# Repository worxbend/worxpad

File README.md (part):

# worxpad

A wireless macropad on its own PCB in a CNC aluminium case. 16 low-profile keys, two knobs with push, two round
buttons, a 240 x 240 colour display, USB-C and Bluetooth to four hosts, a 1,200 mAh battery. Board, case and
firmware are generated from code in this repository and checked against one shared file,
[`board.toml`](board.toml).

It has the function set of the Prota Designs GLYF, which serves as a reference only. Nothing of the GLYF's
name, artwork, firmware or files is used. Where worxpad differs, and why, is in
[Compared with the GLYF](#compared-with-the-glyf) and [docs/reference-device.md](docs/reference-device.md).

*A render of the case model, not a photo. The screen shows a drawing of what the firmware should display.*

> **Status: design files only. Nothing has been built, and the design is not finished.**
> The PCB is placed and routed (DRC clean), but its order files have not been written yet. Two case checks fail. No board has been ordered, no case printed or milled, and the firmware has never
> run on a chip. Every number below is what the design files and their automatic checks say. Read
> [Before you order](#before-you-order) first.

## Contents

1. [Status](#status)
2. [What it is](#what-it-is)
3. [Gallery](#gallery)
4. [Build one](#build-one)
5. [Stock keymap](#stock-keymap)
6. [Work on the design](#work-on-the-design)
7. [What is checked](#what-is-checked)
8. [Where things are](#where-things-are)
9. [Before you order](#before-you-order)
10. [Compared with the GLYF](#compared-with-the-glyf)
11. [License](#license)

## Status

Checked on 2026-11-13. The commands marked "run" were run on this repository for this table. The others are
copied from the last builder run and its report, named in the last column.

| Part | State | How it was checked |
| --- | --- | --- |
| Research and decisions | Done. Seven decision records, a parts summary, a reference dossier; 40 design decisions. | Read; [docs/decisions.md](docs/decisions.md) |
| Specification | Done. `board.toml`: outline, keys, controls, display, module, ports, battery, screws, stack-up, pin map, panel. | Run: `python3 tools/check_spec.py`, 92 of 92 pass |
| Circuit and schematic | Done. 107 parts, 74 nets, 61 machine-placed (31 LCSC codes). Generated KiCad 10 sheet. ERC: 0 errors, 0 warnings. 309 pins match the circuit. | Run: `make pcb-test`, 73 unit tests pass. ERC from the last `build.py schematic`, [pcb/README.md](pcb/README.md) |
| Pin map | Circuit and firmware agree with `board.toml`. | Run: `python3 tools/check_pins.py`, 0 circuit failures, 12 of 12 firmware checks |
| PCB layout | Routed. All 107 parts placed on 4 layers. 1,980 tracks, 280 vias, 0 pads unrouted; short signal hops on both inner layers. DRC: 0 errors, 0 unconnected, 0 schematic differences. No copper in the antenna keep-out. | Run: `make pcb-place` and `make pcb-check`, exit 0 (2026-11-14); `pcb/routing.txt`, [pcb/README.md](pcb/README.md#routing) |
| Board order files | Written. JLCPCB and PCBWay packages, 61 placements in 30 BOM lines (56 on the bottom), panel 135.65 x 95.30 mm with 0 DRC errors, board STEP 1.616 mm thick. | Run: `make pcb-fab`, exit 0 (2026-11-14); [pcb/README.md](pcb/README.md#checks) |
| Case | Model done. 177 of 177 limit checks pass. G1 and G2 pass (tip 0.45 mm against 0.4) only with a proposed bottoming tap that D6 does not yet record. 24 of 24 parts valid, 0 clashes in 666 (CNC) and 703 (FDM) part pairs. Self-test 26 of 26. | Run: `make cad-check` (exit 0); `cad/exports/checks.json`, [cad/README.md](cad/README.md#checks) |
| Firmware | Builds. ZMK 4dd95d78 on Zephyr 10ba6d0c (pinned in `west.yml`). FLASH 391,548 B of 811,008 B (48.28 %), RAM 122,322 B of 262,144 B (46.66 %). UF2 is 783,360 B. | Run: `bash firmware/build.sh` (exit 0); [firmware/README.md](firmware/README.md#build) |
| Pictures | Done. 7 stills, the status screen and a 72-frame turntable; PCB and case pictures. The PCB pictures in `docs/images/pcb/` show the routed board. The renders in `docs/images/renders/` use the routed board's STEP for the board; its parts are still the case package's reference shapes, because the STEP holds no part solids FreeCAD can read. | Run: `make renders`, exit 0 in 1,014 s (2026-11-14) |
| Order package | Files complete. 34 files listed, 0 problems; 30 BOM lines, 61 placements. The gates in [Before you order](#before-you-order) are still open. | Run: `python3 tools/order_package.py`, exit 0 (2026-11-14); [production/README.md](production/README.md) |
| Documentation | Every path and anchor named in Markdown exists. | Run: `make docs-check`, see [What is checked](#what-is-checked) |
| Real hardware | **None.** No board, no print, no flash. | - |

`make test` (spec-check, docs-check, pin-check) exits 0. A passing check says the files agree with each other.
It says nothing about a real part.

The project page, built from `site/` and the pictures in `docs/images/`: <https://worxbend.github.io/worxpad/>
(`make site` builds and checks it locally; see [site/README.md](site/README.md)).

## What it is

| | |
| --- | --- |
| Radio and MCU | u-blox BMD-340-A-R module (nRF52840), PCB trace antenna in a metal-free bay behind a POM insert in a 30 mm slot in the right wall |
| Keys | 16 Kailh Choc V2 class switches at 19.05 mm pitch, hot-swap sockets, 5 x 4 diode matrix (16 keys, 2 knob pushes, 2 buttons) |
| Knobs | 2 x Bourns PEC12R-4215F-S0024, 24 detents, push |
| Buttons | 2 x Omron B3FS-1000P under round caps |
| Display | 1.3 inch 240 x 240 IPS (ST7789V) on a 24-pin FPC, PWM backlight, painted PMMA lens |
| Storage | 16 MB QSPI NOR flash, reserved for icons; the firmware only puts it to sleep today |
| Power | 1,200 mAh LiPo with protection, TI BQ24072 charger with power path (about 400 mA), TPS7A02 3.3 V LDO, MAX17048 gauge, slide switch on the LDO enable |
| USB | USB-C receptacle, ESD array, 0.75 A PTC |
| PCB | 4 layers (In1 ground, In2 3.3 V), parts on both faces, built in a routed frame panel with mouse-bite tabs |
| Case | Two CNC 6061 shells, bead blast and black anodise; 128.4 x 85.2 mm, 20.6 mm at the wedge apex. An FDM PETG variant for a test print |
| Firmware | ZMK: 4 Bluetooth profiles, USB, ZMK Studio over USB and Bluetooth, 4 layers, own status screen. No clock and no widget channel yet |

More detail: [docs/hardware.md](docs/hardware.md).

## Gallery

Every picture is generated by the code in this repository. None is a photo.

### Renders

The status screen is drawn with Pillow from the layout and colours in the firmware source. It is not a
capture from a panel. Materials and colours are proposals. The board in these renders comes from the finished
board STEP; the parts on it are the case package's reference shapes, because FreeCAD reads no part solids from
that STEP. Turntable as
[MP4](docs/images/renders/turntable.mp4). How the renders are made: [tools/render/README.md](tools/render/README.md).

### PCB

These show the routed board (2026-11-14). Parts are block models with nominal heights, not the makers' 3D
models.

Schematic as [PDF](docs/images/pcb/schematic.pdf). Copper layers: [top](docs/images/pcb/copper-top.svg),
[ground](docs/images/pcb/copper-ground.svg), [3.3 V](docs/images/pcb/copper-3v3.svg),
[bottom](docs/images/pcb/copper-bottom.svg). Assembly drawings: [top](docs/images/pcb/assembly-top.svg),
[bottom](docs/images/pcb/assembly-bottom.svg). Routing notes: [pcb/README.md](pcb/README.md).

### Case model

Quick pictures from the case package. The lens is drawn opaque here. More views and the checks:
[cad/README.md](cad/README.md). Machine-shop drawings are in `cad/exports/drawings/`.

## Build one

Nobody has done this yet, and it should not be done today: the order files exist, but gates
below are open. The guides are written from the design files. Expect mistakes.

1. **Read [Before you order](#before-you-order).** Every gate there must be closed.
2. **Check the order package.** `make order` must exit 0. Its index is
   [production/README.md](production/README.md).
3. **Order the board.** [docs/ordering.md](docs/ordering.md): JLCPCB step by step, every form field with its
   reason. Fallback: [docs/ordering-pcbway.md](docs/ordering-pcbway.md). Buy what JLCPCB does not place:
   [docs/parts.md](docs/parts.md) and [docs/bom-hand.csv](docs/bom-hand.csv).
4. **Make the case.** Print the FDM prototype and the coupons first: [docs/printing.md](docs/printing.md).
   Then the CNC shells, knobs and RF insert at JLCCNC, the resin caps at JLC3DP and the lens:
   [docs/ordering-case.md](docs/ordering-case.md).
5. **Assemble, flash and test.** [docs/assembly.md](docs/assembly.md) follows the build order of
   [D28](docs/decisions.md#d28-build-order-cell-orientation-and-lead) and
   [D39](docs/decisions.md#d39-cell-bonded-to-the-pocket-floor-top-assembly-lowered-onto-the-bottom-shell) with a
   bench test at each step.
   Switches go in on the printed insertion jig. [docs/flashing.md](docs/flashing.md): the bootloader once over
   SWD, then `firmware/dist/worxpad.uf2` by drag and drop.

## Stock keymap

Four layers. The right button steps Edit, Nav, Media. Hold the left button for System. The display shows the
knob functions and the 16 key labels of the active layer. Full tables: [docs/keymap.md](docs/keymap.md).

| Layer | Keys, row by row (rear row first) | Left knob: turn, push | Right knob: turn, push |
| --- | --- | --- | --- |
| Edit | Esc Undo Redo SaveAs / Cut Copy Paste Del / Shift Ctrl Alt Space / All Find Tab Enter | Undo, redo; Save | Zoom out, in; Fit |
| Nav | Home Up End PgUp / Left Down Right PgDn / Shift Ctrl Alt Tab / Bksp PrevTab NextTab Enter | Left, right; Space | Up, down; Enter |
| Media | Prev Play Next Mute / Vol- Vol+ Bright- Bright+ / F13 to F16 / F17 to F20 | Volume; Mute | Screen brightness; Play |
| System (hold left button) | Edit Nav Media StudioUnlock / BT1 BT2 BT3 BT4 / BTPrev BTNext BTClear USB-or-BT / USB BT Reset Bootloader | from the layer below | from the layer below |

Shortcuts use Ctrl. Change the keymap in ZMK Studio (unlock on System, row 1, column 4) or in the source
`.keymap` file.

## Work on the design

### Tools

| For | You need |
| --- | --- |
| Checks | Python 3.11 or newer, `make` |
| PCB | Docker. KiCad runs in the pinned image `kicad/kicad:10.0.7` through `pcb/kicad.sh`, with no network |
| Case | Python 3.12 and a venv in `cad/.venv` made with uv, build123d 0.13.0 ([cad/README.md](cad/README.md#build)) |
| Firmware | Docker. `zmkfirmware/zmk-build-arm` pinned by digest. The first build fetches the west modules (about 3 GB) |
| Renders | The case venv, Blender 5.2 and FreeCAD 1.1 as flatpaks, ffmpeg |

Images are pinned by digest in `tools/images.lock`; `bash tools/pull_images.sh <tag>` pulls one.

### Commands

Run `make help` for this list.

| Command | Does | State on 2026-11-14 |
| --- | --- | --- |
| `make test` | spec-check, docs-check, pin-check: everything checkable without Docker or hardware | exits 0 |
| `make pcb-test` | Circuit self-check and generator unit tests, no Docker | exits 0, 73 tests (2026-11-14) |
| `make pcb-place` | Schematic, placed and routed board, DRC, keep-out copper check, PCB pictures | exits 0 (2026-11-14) |
| `make pcb-fab` | Gerbers, drills, panel, JLCPCB and PCBWay files, board STEP | exits 0 |
| `make cad` | Case checks, STEP/STL/3MF exports, drawings, quick pictures (about 7 minutes) | exits 0 |
| `make firmware` | ZMK build into `firmware/dist/worxpad.uf2` | exits 0 |
| `make renders` | Product renders into `docs/images/renders/` (about 15 minutes) | exits 0 |
| `make order` | Order index and CNC package, cross-checks of every order file | exits 0; the gates it cannot check stay open |

Rules for changing the design are in [CLAUDE.md](CLAUDE.md): change `board.toml` first, never hand-edit a
generated file, never weaken a check.

## What is checked

| Area | Check | Result (2026-11-14) |
| --- | --- | --- |
| Specification | `tools/check_spec.py`: keys on pitch, holes and parts inside the outline, no overlapping bodies in a shared Z range, pocket floors against the wedge, stack-up order, RF bay and keep-out, screw-post walls, pin map against the module pad table, 3V3 capacitance, panel and tabs, corner radii for JLCCNC, FDM bed fit | 91 of 91 pass |
| Circuit | `make pcb-test`: circuit self-check, router, schematic writer, footprints, pin map | 73 tests pass |
| Pins | `tools/check_pins.py`: 41 pin map entries, 15 spares and 24 FPC pins against the circuit; GPIOs, pulls, matrix, encoders, display bus and binding counts against the firmware | 0 failures; 12 of 12 |
| Schematic | `kicad-cli sch erc --severity-all`; KiCad's netlist against the circuit | 0 errors, 0 warnings; 309 pins match |
| PCB | `kicad-cli pcb drc --severity-all --schematic-parity`; copper in the antenna keep-out | 0 errors, 0 unconnected, 0 parity; no copper (2026-11-14) |
| Case | `cad/build.py check`: self-test, validity, interference, clearances, CNC rules, FDM rules, RF metal, insertion jig | 177 of 177 limit checks pass; G1 and G2 only with a proposed bottoming tap (D6) |
| Firmware | `firmware/build.sh`: build, UF2 family 0xADA52840 at 0x26000 | pass |
| Orders | `tools/order_package.py`: files present, BOM against CPL, JLCPCB against PCBWay, case checks, hole list | 0 problems, 34 files |
| Docs | `make docs-check`: files, pictures and anchors named in Markdown exist | 674 paths in 48 Markdown files exist (2026-11-14) |

CI ([`.github/workflows/ci.yml`](.github/workflows/ci.yml)) runs `make test`. It has not run on GitHub yet.

## Where things are

| Path | Holds |
| --- | --- |
| [`board.toml`](board.toml) | Single source of truth: positions, stack-up, pin map, matrix, panel |
| [`docs/decisions.md`](docs/decisions.md) | Design decisions D1 to D40 |
| [`pcb/`](pcb/README.md) | The board. `gen/` is the generator (`circuit.py` is the circuit, `layout.py` the placement, `route.py` the routing, `fab.py` the order files), `kicad/` the generated KiCad 10 project, `lib/` footprints, symbols and block models |
| [`cad/`](cad/README.md) | Parametric case (build123d). `worxpad_case/` is the model and its checks, `exports/` holds STEP, STL, 3MF, drawings and `checks.json`, `production/` the JLCCNC package |
| [`firmware/`](firmware/README.md) | ZMK board, keymap, status screen and display power hook in `zmk/`; `build.sh`; `dist/worxpad.uf2` |
| [`production/`](production/README.md) | Generated order index and manifest |
| [`tools/`](tools/) | `check_spec.py`, `check_pins.py`, `check_docs.py`, `order_package.py`, `render_all.sh` and `render/`, pinned images |
| [`docs/hardware.md`](docs/hardware.md) | Circuit in words, pin map, power tree, layer stack, mechanical stack |
| [`docs/parts.md`](docs/parts.md) | Every part, its LCSC number, what to buy elsewhere, cost guesses |
| [`docs/ordering.md`](docs/ordering.md), [`docs/ordering-pcbway.md`](docs/ordering-pcbway.md), [`docs/ordering-case.md`](docs/ordering-case.md) | Ordering the board and the case, field by field |
| [`docs/printing.md`](docs/printing.md) | FDM prototype and coupons |
| [`docs/assembly.md`](docs/assembly.md) | Build order and bench tests |
| [`docs/flashing.md`](docs/flashing.md) | Bootloader over SWD, updates over USB |
| [`docs/keymap.md`](docs/keymap.md) | The stock keymap and how to change it |
| [`docs/reference-device.md`](docs/reference-device.md) | What is known about the GLYF; where worxpad differs |
| [`research/`](research/) | Finished research: `COMPONENTS.md`, `DOSSIER.md`, `components/`, `raw/` |
| `docs/images/` | Generated pictures: `renders/`, `pcb/`, `cad/` |

## Before you order

These are open. None is hidden by a green check.

**Gates: do not order until each is closed**

1. **PCB review.** The board is routed, DRC clean and its order files are written (2026-11-14). A person must
   review the signal hops on the inner layers, the ground island under the module and the vias under the
   module before ordering ([pcb/README.md](pcb/README.md#what-a-person-still-has-to-look-at)).
2. **VBUS on module pad 66 while 3V3 is off** is not read in the nRF52840 Product Specification
   ([D12](docs/decisions.md#d12-vbus-on-module-pad-66-while-the-rail-is-off)).
3. **G1 and G2 thread.** The check passes (tip 0.45 mm against 0.4) only with a proposed bottoming tap that D6
   does not yet record. Needs a decision by the owner
   ([D6](docs/decisions.md#d6-two-ground-screws-with-the-enclosure-numbers), [cad/README.md](cad/README.md#open-items)).
4. **Knob and RF insert tolerances.** The drawings exist; their insert and bore tolerances are proposals that
   nobody has milled or measured.
5. **USB-C plug test.** Plugs with large overmolds may not seat in the 0.25 mm recess. A plug test gates the
   case order ([D37](docs/decisions.md#d37-usb-c-recess-kept-at-025-mm-pending-a-plug-test)).
6. **`make order` exits 0** (it does on 2026-11-14). Run it again after any change; it cross-checks every
   file the vendors receive.

**Electrical**

- **3.3 V rail.** Panel VDD can reach 3.35 V against a 3.3 V recommended maximum
  ([D13](docs/decisions.md#d13-33-v-regulator-accuracy)). The 3V3 capacitance is 21.6 of 22 uF; whether the
  module holds one or two internal 4.7 uF capacitors is not confirmed with u-blox
  ([D14](docs/decisions.md#d14-capacitance-on-the-33-v-rail)).
- **Footprint numbers scaled from drawings (MEASURE):** BMD-340 inner-row step and 4.15 mm column, FH34SRJ
  pad inset, USB-C slot copper ring. Print each footprint 1:1 and lay the part on it. The MAX17048 exposed pad
  is not checked against Maxim's land pattern.
- **Encoder pins and J1.** Encoder pin rows at Y 7.60 collide with J1's shell slots; the layout works round it
  with 1.6 mm pads. The spec check does not catch it.
- **Copper at the board edge.** J1's signal pads and SW18's shield tabs touch the routed edge under a -0.1 mm
  clearance exception. Confirm with JLCPCB.
- **Fine rules.** 0.10 mm track and space everywhere (JLCPCB's 4-layer limit is 0.09 mm), vias under the
  module, short signal hops on both inner planes. The USB pair (D+ 60.58 mm, D- 60.52 mm, matched by a meander)
  has no impedance calculation.
- **Placement rotations.** Only two rows of the JLCPCB rotation table come from a sibling; the rest are
  community values. Check every designator in JLCPCB's placement preview. Confirm the fiducials sit at least
  3.85 mm from the panel edge.
- **Encoder direction** follows KiCad's stock pattern. If a knob counts backwards, swap A and B in firmware.
- **Review.** The schematic and layout are generated and machine-checked. No engineer has reviewed them.

**Mechanical**

- **Antenna inset** depends on the +/-0.2 mm routed outline
  ([D24](docs/decisions.md#d24-antenna-inset-against-the-outline-tolerance)); ask JLCPCB for +/-0.1 mm.
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
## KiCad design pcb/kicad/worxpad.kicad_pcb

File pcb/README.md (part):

# PCB

**Not built.** No board has been ordered, assembled or powered. This page says what the design files hold
and which automatic checks ran on them, nothing more. A clean rule check does not make a working board.

The PCB is generated. Nothing in `pcb/kicad/` is drawn by hand: `pcb/gen/` writes the schematic, the project
footprints and symbols, and the pictures from two inputs, `board.toml` (positions, pin map) and
`pcb/gen/circuit.py` (parts and nets).

State on 2026-11-14: circuit, footprints, symbols and schematic are done (PCB part 1). The board is placed
and **routed**: `make pcb-place` reports no unrouted pad, and `make pcb-check` finds 0 violations, 0 unconnected
items and 0 schematic parity issues. `make pcb-fab` wrote pcb/fab and pcb/production from it (2026-11-14). See [Board](#board-pcb-part-2) and [Routing](#routing).

The schematic, one A2 sheet in 14 blocks. [PDF](../docs/images/pcb/schematic.pdf),
[SVG](../docs/images/pcb/schematic.svg). It is a drawing of `pcb/gen/circuit.py`, not a second source of truth.

## Commands

| Command | Needs | What it does |
|---|---|---|
| `make pcb-test` | Python 3.11+ | Netlist self-checks, the 3V3 capacitance sum (D14), `tools/check_pins.py`, 73 unit tests. |
| `pcb/kicad.sh python3 pcb/gen/build.py schematic` | Docker | Footprints written and read back, schematic, ERC, netlist compare, PDF and SVG, block models. About 7 s. |
| `make pcb-place` | Docker | Schematic step, placed and routed board, planes filled, DRC with schematic parity, RF keep-out copper check, pictures in `docs/images/pcb/`, `pcb/routing.txt`. About 6 min (372 s on 2026-11-14, another job running). Fails while any pad is unrouted. |
| `pcb/kicad.sh python3 pcb/gen/build.py order` | Docker | Routes again and again, moving walled-in nets to the front; writes the best order to `pcb/gen/route_order.txt`. Several minutes per round. |
| `make pcb-fab` | Docker | Gerbers, drills, panel, JLCPCB and PCBWay files, board STEP. Refuses a board whose last DRC has an error, an unconnected item or a parity finding. |
| `pcb/kicad.sh python3 pcb/gen/build.py fab-draft` | Docker | The same files under `pcb/.build/draft/`, for testing the generator on an unfinished board. Never an order. |

`pcb/kicad.sh` runs `kicad/kicad:10.0.7` by the digest in `tools/images.lock`, with `--network none` and
`PYTHONHASHSEED=0`, and runs `tools/kicad_env.sh` first.

## Files

| Path | What |
|---|---|
| `pcb/gen/circuit.py` | Every part: value, JLCPCB number, footprint, face, board.toml position, nets. Pure Python. |
| `pcb/gen/footprints.py` | Writes the six project footprints into `pcb/lib/worxpad.pretty/`. Pure Python. |
| `pcb/gen/schematic.py` | Writes the KiCad 10 schematic, the project symbol library and the library tables. |
| `pcb/gen/sheet_layout.py` | Where each part sits on the sheet and which wires are drawn. Data only. |
| `pcb/gen/symlib.py`, `pcb/gen/sexpr.py` | Read KiCad symbol libraries; draw box symbols. From macropad, unchanged. |
| `pcb/gen/layout.py` | Placement: board.toml positions, the spots board.toml leaves open, outline, planes, placement asserts. |
| `pcb/gen/route.py` | Routing order and stages, rip-up and reroute, plane island repair, the copper writer. |
| `pcb/gen/router.py` | Grid router from macropad: outer layers plus short hops on both inner layers, escapes, rip-up with history costs, meanders, plane area check, `close_outside` for this outline. |
| `pcb/gen/route_order.txt` | Nets routed first: the key matrix, seeded by hand. |
| `pcb/gen/fab.py` | Gerbers, drills, the D23 panel, BOM, CPL with the rotation table, PCBWay files, STEP. |
| `pcb/kicad/worxpad.kicad_pcb` | Generated board. `pcb/kicad/worxpad.kicad_dru`: the two edge-clearance exceptions. |
| `pcb/routing.txt` | Generated routing report: tracks, vias, length per net, unrouted pads. |
| `pcb/gen/models.py` | Block 3D models (VRML) per footprint type, into `pcb/lib/3d/`. |
| `pcb/gen/build.py` | The steps above. |
| `pcb/gen/test_*.py` | Router (26), schematic writer (21) and circuit, footprint and pin-map tests (26). |
| `pcb/lib/SOURCES.txt` | Where every project footprint number comes from. |
| `pcb/kicad/` | Generated KiCad 10 project: schematic, library tables. |
| `pcb/netlist.txt` | Generated netlist, one line per net. |

## The circuit

Sources are the records in `research/components/` and `docs/decisions.md`. In short:

- **Radio:** u-blox BMD-340 in LV mode, VCC and VCCH on 3V3, 10 uF bulk, 32.768 kHz crystal with 2 x 20 pF,
  pin reset on P0.18, SWD on a TC2030-NL pad set. USB D+/D- and VBUS (pad 66) after the ESD array and PTC.
- **Flash:** W25Q128JVSIQ on QSPI with 100 nF.
- **Display:** FH34SRJ-24S, pin map from `board.toml` `display.fpc_pins`; AO3400A low-side backlight switch
  with 100k gate pull-down, 15 Ohm to LEDA, 1 uF and 100 nF at VDD.
- **USB-C:** HRO TYPE-C-31-M-13C, 5.1k on CC1 and CC2, USBLC6-2SC6 before the 1206L075 PTC, shell to GND.
- **Power:** BQ24072 (USB500, ISET 2.2k, ILIM 3.3k, EN1 100k from IN, TMR open, NTC on TS), AO3401A in the
  cell's positive line, JST PH (pin 1 positive), TPS7A0233 with its EN on the MSK12C02 slide switch,
  MAX17048 on BAT with 4.7k pull-ups to 3V3. 3V3 holds 21.6 uF nominal including the module's 9.4 uF (D14);
  the build fails if a capacitor is added or removed on 3V3 without changing `board.toml`.
- **Inputs:** 4 x 5 col2row matrix, one 1N4148W per position. Column 4: right encoder push R0, left encoder push
  R1, right button R2, left button R3 (D20). PEC12R-4215F encoders with A/B on P0.29/P0.31 (right) and
  P0.28/P0.30 (left); 10 nF filter footprints, not fitted (D36).
- **Other:** 11 test pads, eight holes (K and C NPTH 4.0, G plated with GND rings), six fiducials.

107 parts: 61 machine-placed (31 distinct JLCPCB numbers, the two THT encoders included), 16 hand-fitted
sockets, 4 not-fitted footprints, 26 pads, holes and fiducials.

## Symbols and footprints

Stock KiCad 10.0.7 symbols for every part that has one. Three box symbols are drawn in `pcb/gen/schematic.py`
and written to the generated `pcb/lib/worxpad.kicad_sym`: BMD-340 (pins from `board.toml` `[module.pads]`),
TPS7A02 (DBV pin order) and MAX17048 (TDFN pin table).

Stock footprints where KiCad has one, including the TC2030-NL pad set and the MSK12C02 switch. Six project
footprints in `pcb/lib/worxpad.pretty/`, sources in `pcb/lib/SOURCES.txt`: BMD-340 with its RF keep-out rule
area, FH34SRJ-24S, TYPE-C-31-M-13C, Choc V2 hot-swap, PEC12R-4 and the plated G hole.

## Checks

| Check | Where | Result (2026-11-13 and 2026-11-14, real runs) |
|---|---|---|
| No single-pad net, no duplicate reference | `circuit.check_netlist` | pass, 107 parts, 74 nets |
| 3V3 capacitors equal `power.rail_3v3_caps_uf`, sum under 22 uF | `circuit.check_rail_capacitance` | pass, 21.6 uF |
| Pin map: pads, nets, spares, fast pins, matrix, encoders, FPC pins | `tools/check_pins.py` | pass, 41 entries, 15 spares, 24 FPC pins |
| Each part's pins exist on its symbol; footprint matches the symbol's | `schematic.check_part_against_symbol` | pass |
| BMD-340 symbol (pin table) and footprint (figures 2, 12) name the same 68 pads | `schematic.check_module_symbol` | pass |
| Every project footprint loads in pcbnew with the pads that were meant | `build.write_footprints` | pass, 6 footprints |
| `kicad-cli sch erc --severity-all` | `build.py schematic` | 0 errors, 0 warnings |
| KiCad's exported netlist against `circuit.py`, pin by pin | `build.py schematic` | pass, 309 pins, 23 open pins |
| Unit tests | `make pcb-test` | 73 pass (2026-11-14) |
| Placement asserts: faces, antenna end and keep-out, J2 contact 1 and entry, socket mirroring, J1 edge and mouth, J3 mouth and body centre, SW18 actuator, hole keep-outs, J4 low zone, RF bay | `layout.check_placement` | pass |
| Router closes the USB notch and keeps the board middle open | `route.new_router` | pass |
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
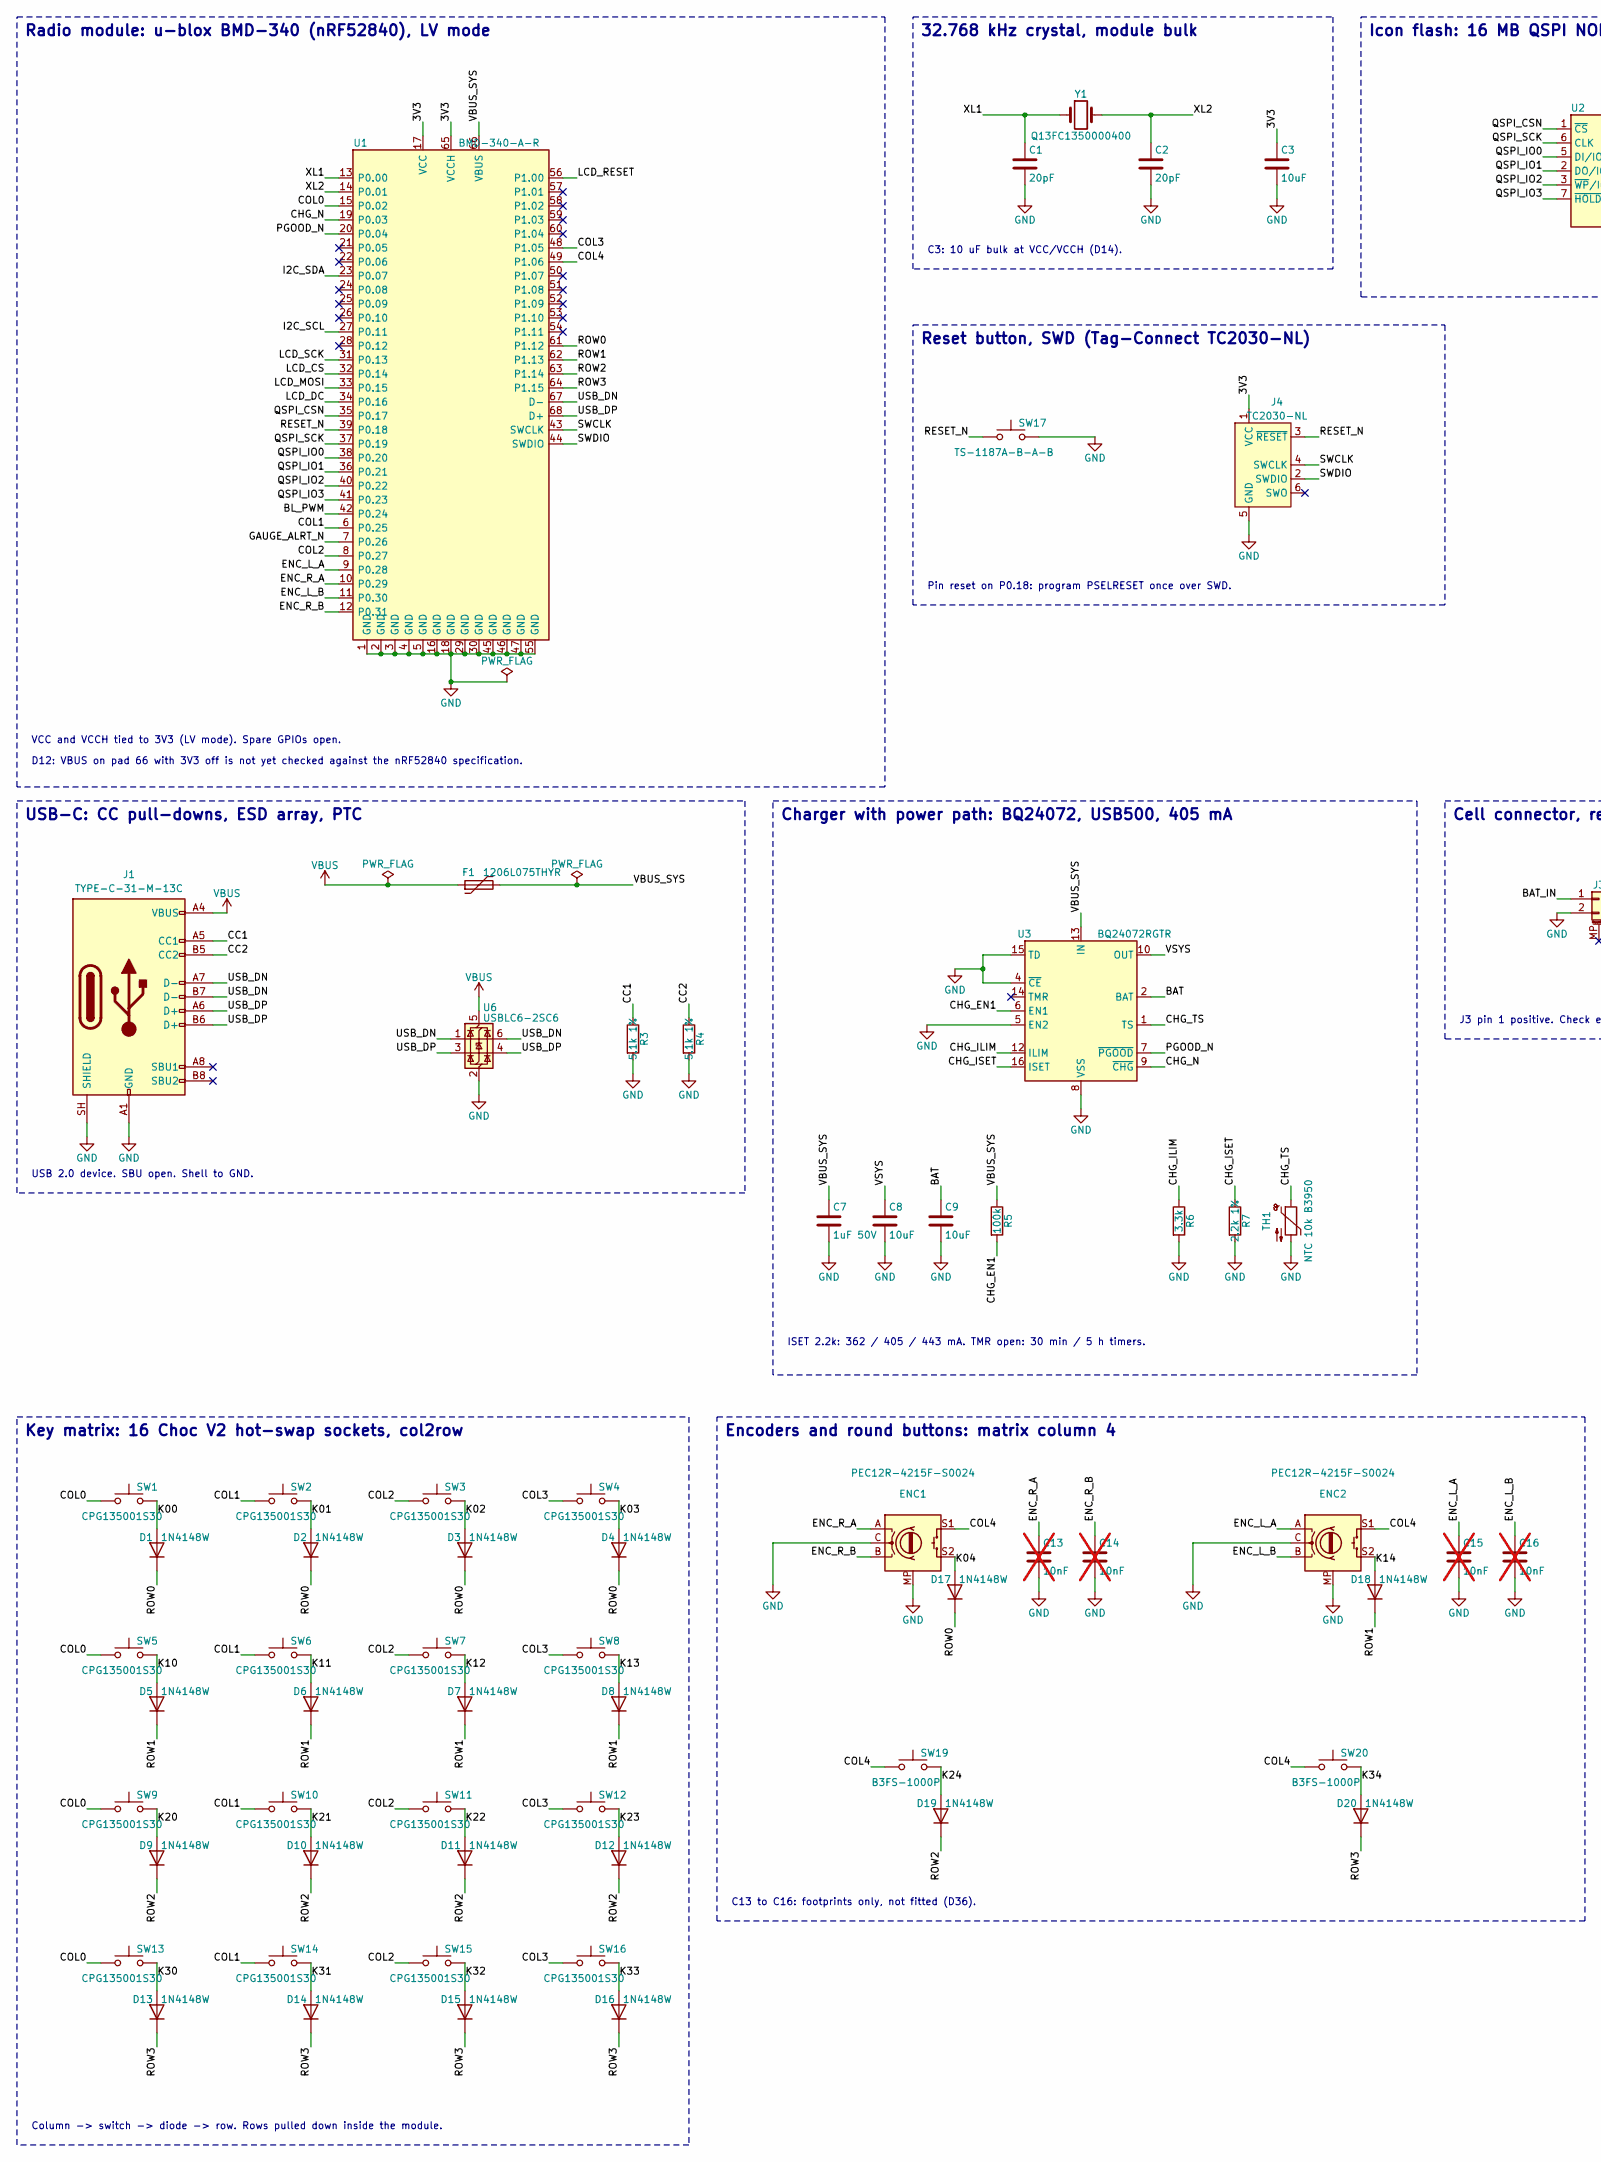
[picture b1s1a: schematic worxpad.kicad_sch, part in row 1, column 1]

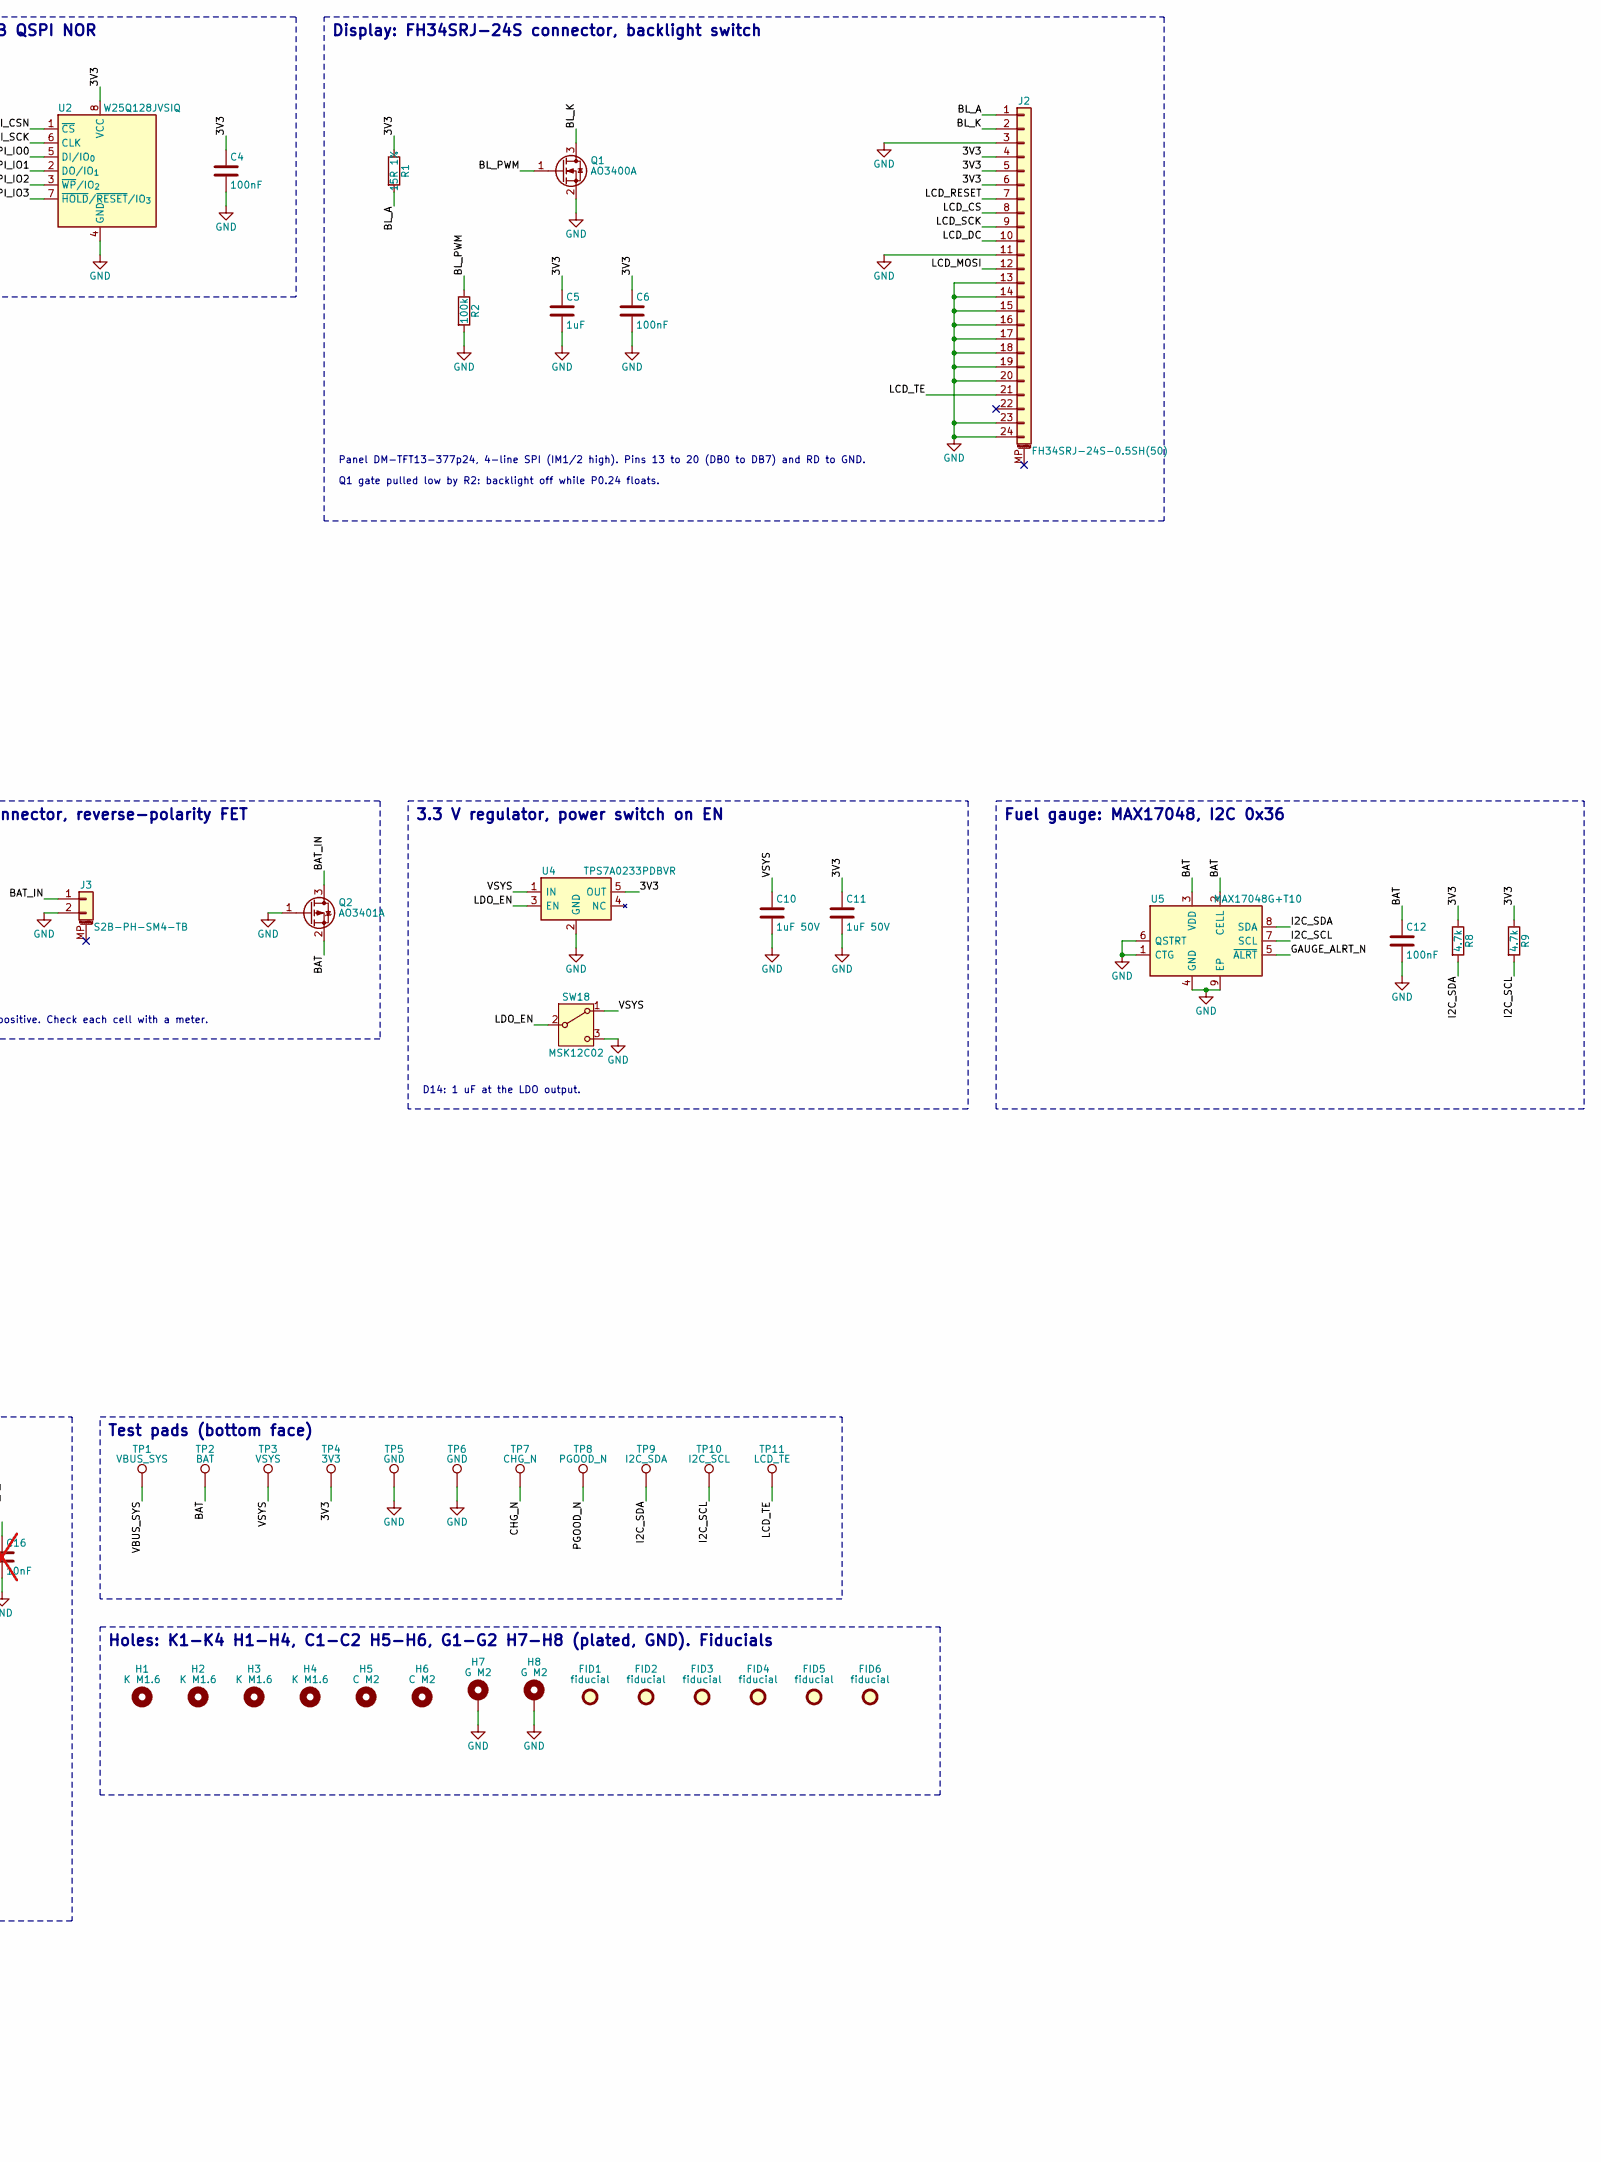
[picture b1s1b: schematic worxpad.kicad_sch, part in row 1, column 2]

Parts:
C1, C2: 20pF; C_0402_1005Metric; LCSC C1554
C3, C8, C9: 10uF; C_0603_1608Metric; LCSC C19702
C4, C6, C12: 100nF; C_0402_1005Metric; LCSC C1525
C5: 1uF; C_0402_1005Metric; LCSC C52923
C7, C10, C11: 1uF 50V; C_0603_1608Metric; LCSC C15849
C13, C14, C15, C16: 10nF; C_0402_1005Metric; not fitted
D1, D2, D3, D4, D5, D6, D7, D8, D9, D10, D11, D12, D13, D14, D15, D16, D17, D18, D19, D20: 1N4148W; D_SOD-123; LCSC C81598
ENC1, ENC2: PEC12R-4215F-S0024; PEC12R-4xxxF-S; LCSC C22385080
F1: 1206L075THYR; Fuse_1206_3216Metric; LCSC C99563
FID1, FID2, FID3, FID4, FID5, FID6: fiducial; Fiducial_1mm_Mask2mm
H1, H2, H3, H4: K M1.6; MountingHole_4mm
H5, H6: C M2; MountingHole_4mm
H7, H8: G M2; Hole_G_M2_Plated
J1: TYPE-C-31-M-13C; USB_C_HRO_TYPE-C-31-M-13C; LCSC C2848620
J2: FH34SRJ-24S-0.5SH(50); FH34SRJ-24S-0.5SH; LCSC C324726
J3: S2B-PH-SM4-TB; JST_PH_S2B-PH-SM4-TB_1x02-1MP_P2.00mm_Horizontal; LCSC C295747
J4: TC2030-NL; Tag-Connect_TC2030-IDC-NL_2x03_P1.27mm_Vertical
Q1: AO3400A; SOT-23; LCSC C20917
Q2: AO3401A; SOT-23; LCSC C15127
R1: 15R 1%; R_0402_1005Metric; LCSC C25083
R2, R5: 100k; R_0402_1005Metric; LCSC C25741
R3, R4: 5.1k 1%; R_0402_1005Metric; LCSC C25905
R6: 3.3k; R_0402_1005Metric; LCSC C25890
R7: 2.2k 1%; R_0402_1005Metric; LCSC C25879
R8, R9: 4.7k; R_0402_1005Metric; LCSC C25900
SW1, SW2, SW3, SW4, SW5, SW6, SW7, SW8, SW9, SW10, SW11, SW12, SW13, SW14, SW15, SW16: CPG135001S30; Choc_V2_Hotswap; LCSC C5333465
SW17: TS-1187A-B-A-B; SW_Push_1P1T_XKB_TS-1187A; LCSC C318884
SW18: MSK12C02; SW_SPDT_Shouhan_MSK12C02; LCSC C431540
SW19, SW20: B3FS-1000P; SW_SPST_Omron_B3FS-100xP; LCSC C271750
TH1: NTC 10k B3950; R_0805_2012Metric; LCSC C51597
TP1: VBUS_SYS; TestPoint_Pad_D1.0mm
TP2: BAT; TestPoint_Pad_D1.0mm
TP3: VSYS; TestPoint_Pad_D1.0mm
TP4: 3V3; TestPoint_Pad_D1.0mm
TP5, TP6: GND; TestPoint_Pad_D1.0mm
TP7: CHG_N; TestPoint_Pad_D1.0mm
TP8: PGOOD_N; TestPoint_Pad_D1.0mm
TP9: I2C_SDA; TestPoint_Pad_D1.0mm
TP10: I2C_SCL; TestPoint_Pad_D1.0mm
TP11: LCD_TE; TestPoint_Pad_D1.0mm
U1: BMD-340-A-R; BMD-340; LCSC C5456944
U2: W25Q128JVSIQ; SOIC-8_5.3x5.3mm_P1.27mm; LCSC C97521
U3: BQ24072RGTR; VQFN-16-1EP_3x3mm_P0.5mm_EP1.6x1.6mm; LCSC C140288
U4: TPS7A0233PDBVR; SOT-23-5; LCSC C2887324
U5: MAX17048G+T10; DFN-8-1EP_2x2mm_P0.5mm_EP0.8x1.6mm; LCSC C2682616
U6: USBLC6-2SC6; SOT-23-6; LCSC C7519
Y1: Q13FC1350000400; Crystal_SMD_3215-2Pin_3.2x1.5mm; LCSC C32346

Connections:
/3V3: C3.1, C4.1, C5.1, C6.1, C11.1, J2.4, J2.5, J2.6, J4.1 (VCC), R1.1, R8.1, R9.1, TP4.1, U1.17 (VCC), U1.65 (VCCH), U2.8 (VCC), U4.5 (OUT)
/BAT: C9.1, C12.1, Q2.2 (S), TP2.1, U3.2 (BAT), U3.3 (BAT), U5.2 (CELL), U5.3 (VDD)
/BAT_IN: J3.1, Q2.3 (D)
/BL_A: J2.1, R1.2
/BL_K: J2.2, Q1.3 (D)
/BL_PWM: Q1.1 (G), R2.1, U1.42 (P0.24)
/CC1: J1.A5 (CC1), R3.1
/CC2: J1.B5 (CC2), R4.1
/CHG_EN1: R5.2, U3.6 (EN1)
/CHG_ILIM: R6.1, U3.12 (ILIM)
/CHG_ISET: R7.1, U3.16 (ISET)
/CHG_N: TP7.1, U1.19 (P0.03), U3.9 (~CHG)
/CHG_TS: TH1.1, U3.1 (TS)
/COL0: SW1.1, SW5.1, SW9.1, SW13.1, U1.15 (P0.02)
/COL1: SW2.1, SW6.1, SW10.1, SW14.1, U1.6 (P0.25)
/COL2: SW3.1, SW7.1, SW11.1, SW15.1, U1.8 (P0.27)
/COL3: SW4.1, SW8.1, SW12.1, SW16.1, U1.48 (P1.05)
/COL4: ENC1.S1, ENC2.S1, SW19.1, SW20.1, U1.49 (P1.06)
/ENC_L_A: C15.1, ENC2.A, U1.9 (P0.28)
/ENC_L_B: C16.1, ENC2.B, U1.11 (P0.30)
/ENC_R_A: C13.1, ENC1.A, U1.10 (P0.29)
/ENC_R_B: C14.1, ENC1.B, U1.12 (P0.31)
/GAUGE_ALRT_N: U1.7 (P0.26), U5.5 (~ALRT)
/I2C_SCL: R9.2, TP10.1, U1.27 (P0.11), U5.7 (SCL)
/I2C_SDA: R8.2, TP9.1, U1.23 (P0.07), U5.8 (SDA)
/K00: D1.2 (A), SW1.2
/K01: D2.2 (A), SW2.2
/K02: D3.2 (A), SW3.2
/K03: D4.2 (A), SW4.2
/K04: D17.2 (A), ENC1.S2
/K10: D5.2 (A), SW5.2
/K11: D6.2 (A), SW6.2
/K12: D7.2 (A), SW7.2
/K13: D8.2 (A), SW8.2
/K14: D18.2 (A), ENC2.S2
/K20: D9.2 (A), SW9.2
/K21: D10.2 (A), SW10.2
/K22: D11.2 (A), SW11.2
/K23: D12.2 (A), SW12.2
/K24: D19.2 (A), SW19.2
/K30: D13.2 (A), SW13.2
/K31: D14.2 (A), SW14.2
/K32: D15.2 (A), SW15.2
/K33: D16.2 (A), SW16.2
/K34: D20.2 (A), SW20.2
/LCD_CS: J2.8, U1.32 (P0.14)
/LCD_DC: J2.10, U1.34 (P0.16)
/LCD_MOSI: J2.12, U1.33 (P0.15)
/LCD_RESET: J2.7, U1.56 (P1.00)
/LCD_SCK: J2.9, U1.31 (P0.13)
/LCD_TE: J2.21, TP11.1
/LDO_EN: SW18.2 (B), U4.3 (EN)
/PGOOD_N: TP8.1, U1.20 (P0.04), U3.7 (~PGOOD)
/QSPI_CSN: U1.35 (P0.17), U2.1 (~CS)
/QSPI_IO0: U1.38 (P0.20), U2.5 (DI/IO_{0})
/QSPI_IO1: U1.36 (P0.21), U2.2 (DO/IO_{1})
/QSPI_IO2: U1.40 (P0.22), U2.3 (~WP/IO_{2})
/QSPI_IO3: U1.41 (P0.23), U2.7 (~HOLD/~RESET/IO_{3})
/QSPI_SCK: U1.37 (P0.19), U2.6 (CLK)
/RESET_N: J4.3 (~RESET), SW17.1, U1.39 (P0.18)
/ROW0: D1.1 (K), D2.1 (K), D3.1 (K), D4.1 (K), D17.1 (K), U1.61 (P1.12)
/ROW1: D5.1 (K), D6.1 (K), D7.1 (K), D8.1 (K), D18.1 (K), U1.62 (P1.13)
/ROW2: D9.1 (K), D10.1 (K), D11.1 (K), D12.1 (K), D19.1 (K), U1.63 (P1.14)
/ROW3: D13.1 (K), D14.1 (K), D15.1 (K), D16.1 (K), D20.1 (K), U1.64 (P1.15)
/SWCLK: J4.4 (SWCLK), U1.43 (SWCLK)
/SWDIO: J4.2 (SWDIO), U1.44 (SWDIO)
/USB_DN: J1.A7 (D-), J1.B7 (D-), U1.67 (D-), U6.1 (I/O1), U6.6 (I/O1)
/USB_DP: J1.A6 (D+), J1.B6 (D+), U1.68 (D+), U6.3 (I/O2), U6.4 (I/O2)
/VBUS_SYS: C7.1, F1.2, R5.1, TP1.1, U1.66 (VBUS), U3.13 (IN)
/VSYS: C8.1, C10.1, SW18.1 (A), TP3.1, U3.10 (OUT), U3.11 (OUT), U4.1 (IN)
/XL1: C1.1, U1.13 (P0.00), Y1.1
/XL2: C2.1, U1.14 (P0.01), Y1.2
GND: C1.2, C2.2, C3.2, C4.2, C5.2, C6.2, C7.2, C8.2, C9.2, C10.2, C11.2, C12.2, C13.2, C14.2, C15.2, C16.2, ENC1.C, ENC1.MP, ENC2.C, ENC2.MP, H7.1, H8.1, J1.A1 (GND), J1.A12 (GND), J1.B1 (GND), J1.B12 (GND), J1.SH (SHIELD), J2.3, J2.11, J2.13, J2.14, J2.15, J2.16, J2.17, J2.18, J2.19, J2.20, J2.23, J2.24, J3.2, J4.5 (GND), Q1.2 (S), Q2.1 (G), R2.2, R3.2, R4.2, R6.2, R7.2, SW17.2, SW18.3 (C), TH1.2, TP5.1, TP6.1, U1.1 (GND), U1.2 (GND), U1.3 (GND), U1.4 (GND), U1.5 (GND), U1.16 (GND), U1.18 (GND), U1.29 (GND), U1.30 (GND), U1.45 (GND), U1.46 (GND), U1.47 (GND), U1.55 (GND), U2.4 (GND), U3.4 (~CE), U3.5 (EN2), U3.8 (VSS), U3.15 (TD), U3.17 (VSS), U4.2 (GND), U5.1 (CTG), U5.4 (GND), U5.6 (QSTRT), U5.9 (EP), U6.2 (GND)
VBUS: F1.1, J1.A4 (VBUS), J1.A9 (VBUS), J1.B4 (VBUS), J1.B9 (VBUS), U6.5 (VBUS)

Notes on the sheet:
Radio module: u-blox BMD-340 (nRF52840), LV mode
VCC and VCCH tied to 3V3 (LV mode). Spare GPIOs open.
D12: VBUS on pad 66 with 3V3 off is not yet checked against the nRF52840 specification.
32.768 kHz crystal, module bulk
C3: 10 uF bulk at VCC/VCCH (D14).
Icon flash: 16 MB QSPI NOR
Display: FH34SRJ-24S connector, backlight switch
Panel DM-TFT13-377p24, 4-line SPI (IM1/2 high). Pins 13 to 20 (DB0 to DB7) and RD to GND.
Q1 gate pulled low by R2: backlight off while P0.24 floats.
Reset button, SWD (Tag-Connect TC2030-NL)
Pin reset on P0.18: program PSELRESET once over SWD.
USB-C: CC pull-downs, ESD array, PTC
USB 2.0 device. SBU open. Shell to GND.
Charger with power path: BQ24072, USB500, 405 mA
ISET 2.2k: 362 / 405 / 443 mA. TMR open: 30 min / 5 h timers.
Cell connector, reverse-polarity FET
J3 pin 1 positive. Check each cell with a meter.
3.3 V regulator, power switch on EN
D14: 1 uF at the LDO output.
Fuel gauge: MAX17048, I2C 0x36
Key matrix: 16 Choc V2 hot-swap sockets, col2row
Column -> switch -> diode -> row. Rows pulled down inside the module.
Encoders and round buttons: matrix column 4
C13 to C16: footprints only, not fitted (D36).
Test pads (bottom face)
Holes: K1-K4 H1-H4, C1-C2 H5-H6, G1-G2 H7-H8 (plated, GND). Fiducials

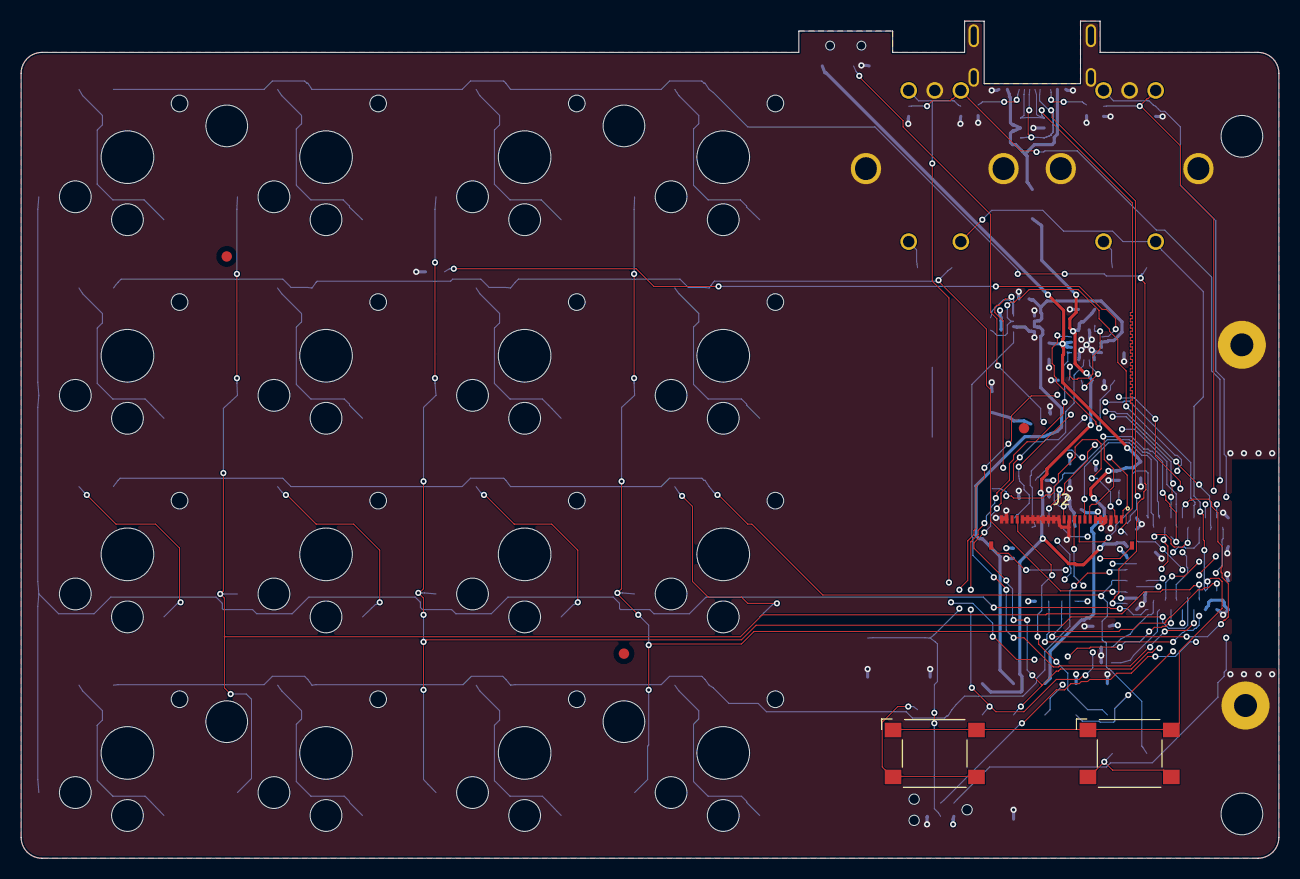
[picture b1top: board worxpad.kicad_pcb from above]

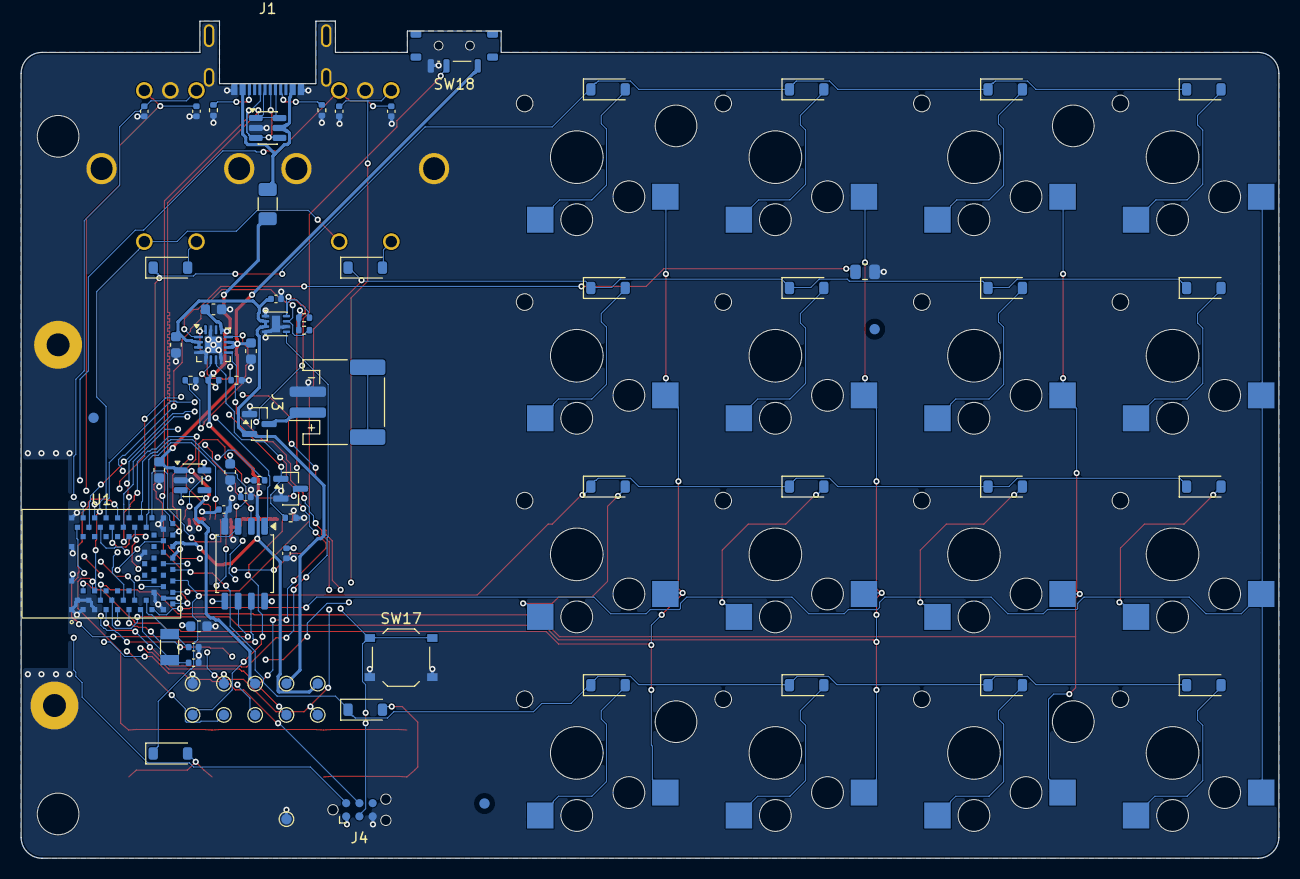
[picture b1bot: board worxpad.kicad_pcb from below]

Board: 4 copper layers, 120.7 x 80.3 mm, 107 parts (91 on the bottom side), 74 nets.

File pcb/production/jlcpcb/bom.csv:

Comment,Designator,Footprint,LCSC Part #
100k,"R2,R5",R_0402_1005Metric,C25741
100nF,"C4,C6,C12",C_0402_1005Metric,C1525
10uF,"C3,C8,C9",C_0603_1608Metric,C19702
1206L075THYR,F1,Fuse_1206_3216Metric,C99563
15R 1%,R1,R_0402_1005Metric,C25083
1N4148W,"D1,D2,D3,D4,D5,D6,D7,D8,D9,D10,D11,D12,D13,D14,D15,D16,D17,D18,D19,D20",D_SOD-123,C81598
1uF,C5,C_0402_1005Metric,C52923
1uF 50V,"C7,C10,C11",C_0603_1608Metric,C15849
2.2k 1%,R7,R_0402_1005Metric,C25879
20pF,"C1,C2",C_0402_1005Metric,C1554
3.3k,R6,R_0402_1005Metric,C25890
4.7k,"R8,R9",R_0402_1005Metric,C25900
5.1k 1%,"R3,R4",R_0402_1005Metric,C25905
AO3400A,Q1,SOT-23,C20917
AO3401A,Q2,SOT-23,C15127
B3FS-1000P,"SW19,SW20",SW_SPST_Omron_B3FS-100xP,C271750
BMD-340-A-R,U1,BMD-340,C5456944
BQ24072RGTR,U3,VQFN-16-1EP_3x3mm_P0.5mm_EP1.6x1.6mm,C140288
FH34SRJ-24S-0.5SH(50),J2,FH34SRJ-24S-0.5SH,C324726
MAX17048G+T10,U5,DFN-8-1EP_2x2mm_P0.5mm_EP0.8x1.6mm,C2682616
MSK12C02,SW18,SW_SPDT_Shouhan_MSK12C02,C431540
NTC 10k B3950,TH1,R_0805_2012Metric,C51597
PEC12R-4215F-S0024,"ENC1,ENC2",PEC12R-4xxxF-S,C22385080
Q13FC1350000400,Y1,Crystal_SMD_3215-2Pin_3.2x1.5mm,C32346
S2B-PH-SM4-TB,J3,JST_PH_S2B-PH-SM4-TB_1x02-1MP_P2.00mm_Horizontal,C295747
TPS7A0233PDBVR,U4,SOT-23-5,C2887324
TS-1187A-B-A-B,SW17,SW_Push_1P1T_XKB_TS-1187A,C318884
TYPE-C-31-M-13C,J1,USB_C_HRO_TYPE-C-31-M-13C,C2848620
USBLC6-2SC6,U6,SOT-23-6,C7519
W25Q128JVSIQ,U2,SOIC-8_5.3x5.3mm_P1.27mm,C97521

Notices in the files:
README.md:
License:
Code (scripts, generators): GPL-3.0-or-later, see [LICENSE](LICENSE). Hardware (board, case, drawings):
CERN-OHL-S-2.0, see [LICENSE-HARDWARE](LICENSE-HARDWARE). The ZMK files under `firmware/zmk` are MIT, as ZMK
is. Third-party material is listed in [THIRD_PARTY.md](THIRD_PARTY.md). The owner has to confirm this choice.
GLYF and Prota Designs are names of their owner. worxpad is not affiliated with them.
